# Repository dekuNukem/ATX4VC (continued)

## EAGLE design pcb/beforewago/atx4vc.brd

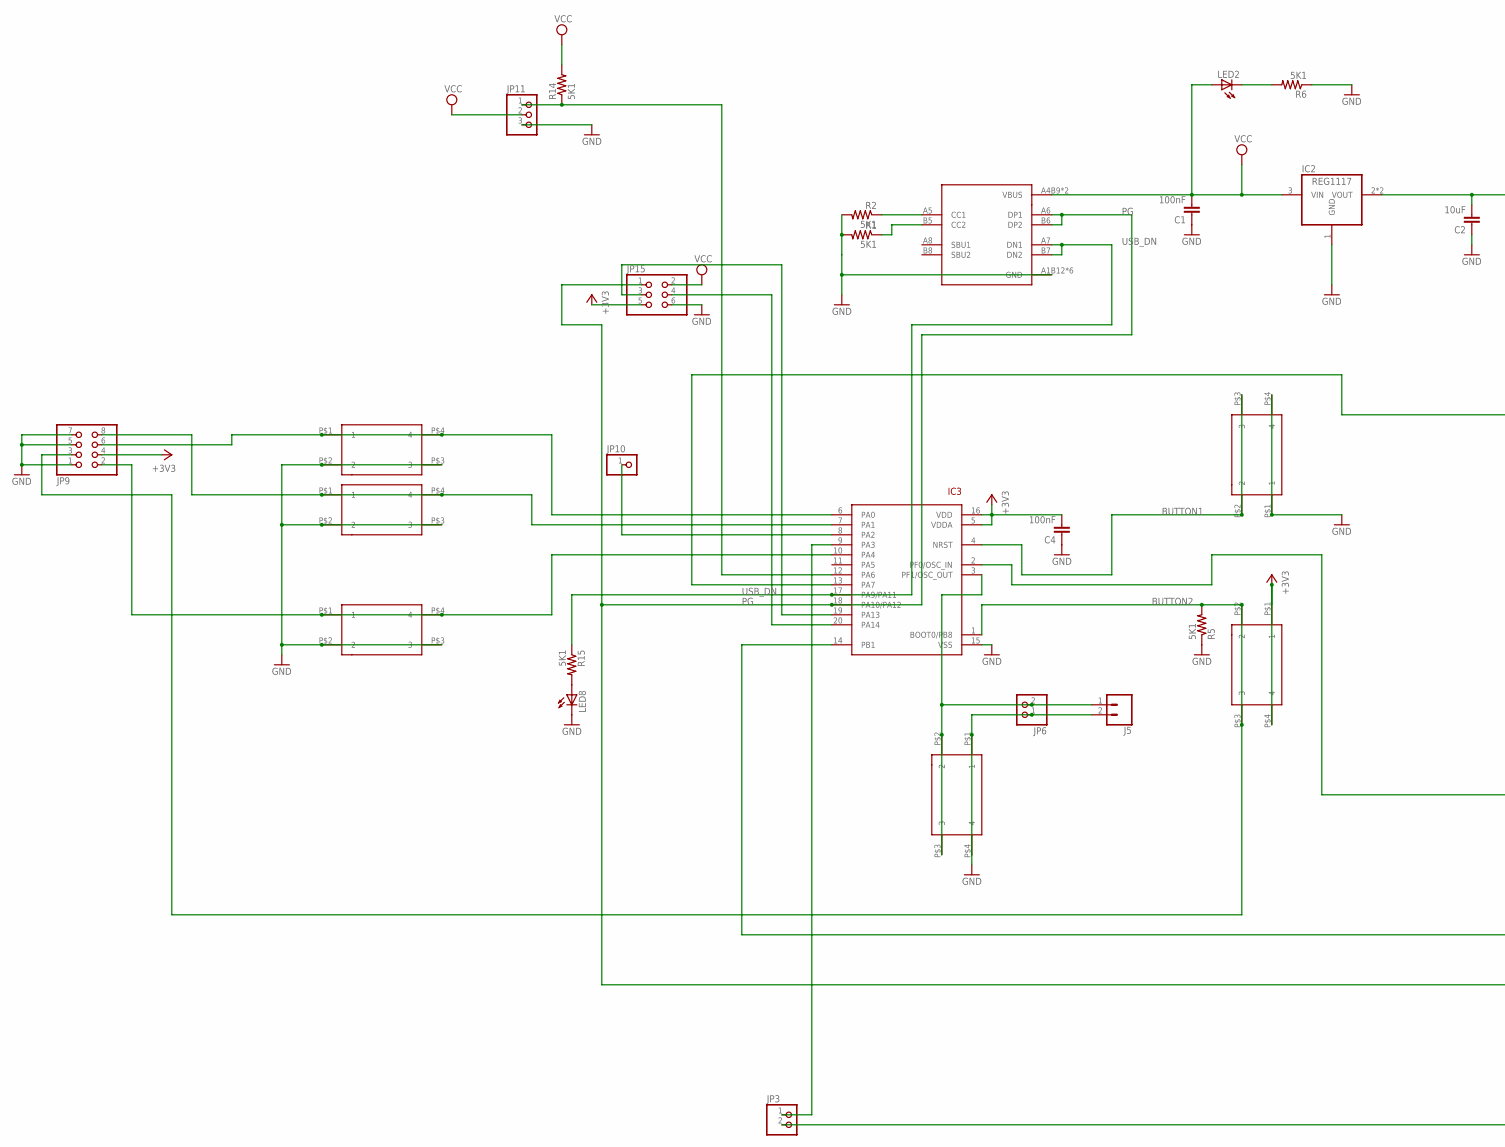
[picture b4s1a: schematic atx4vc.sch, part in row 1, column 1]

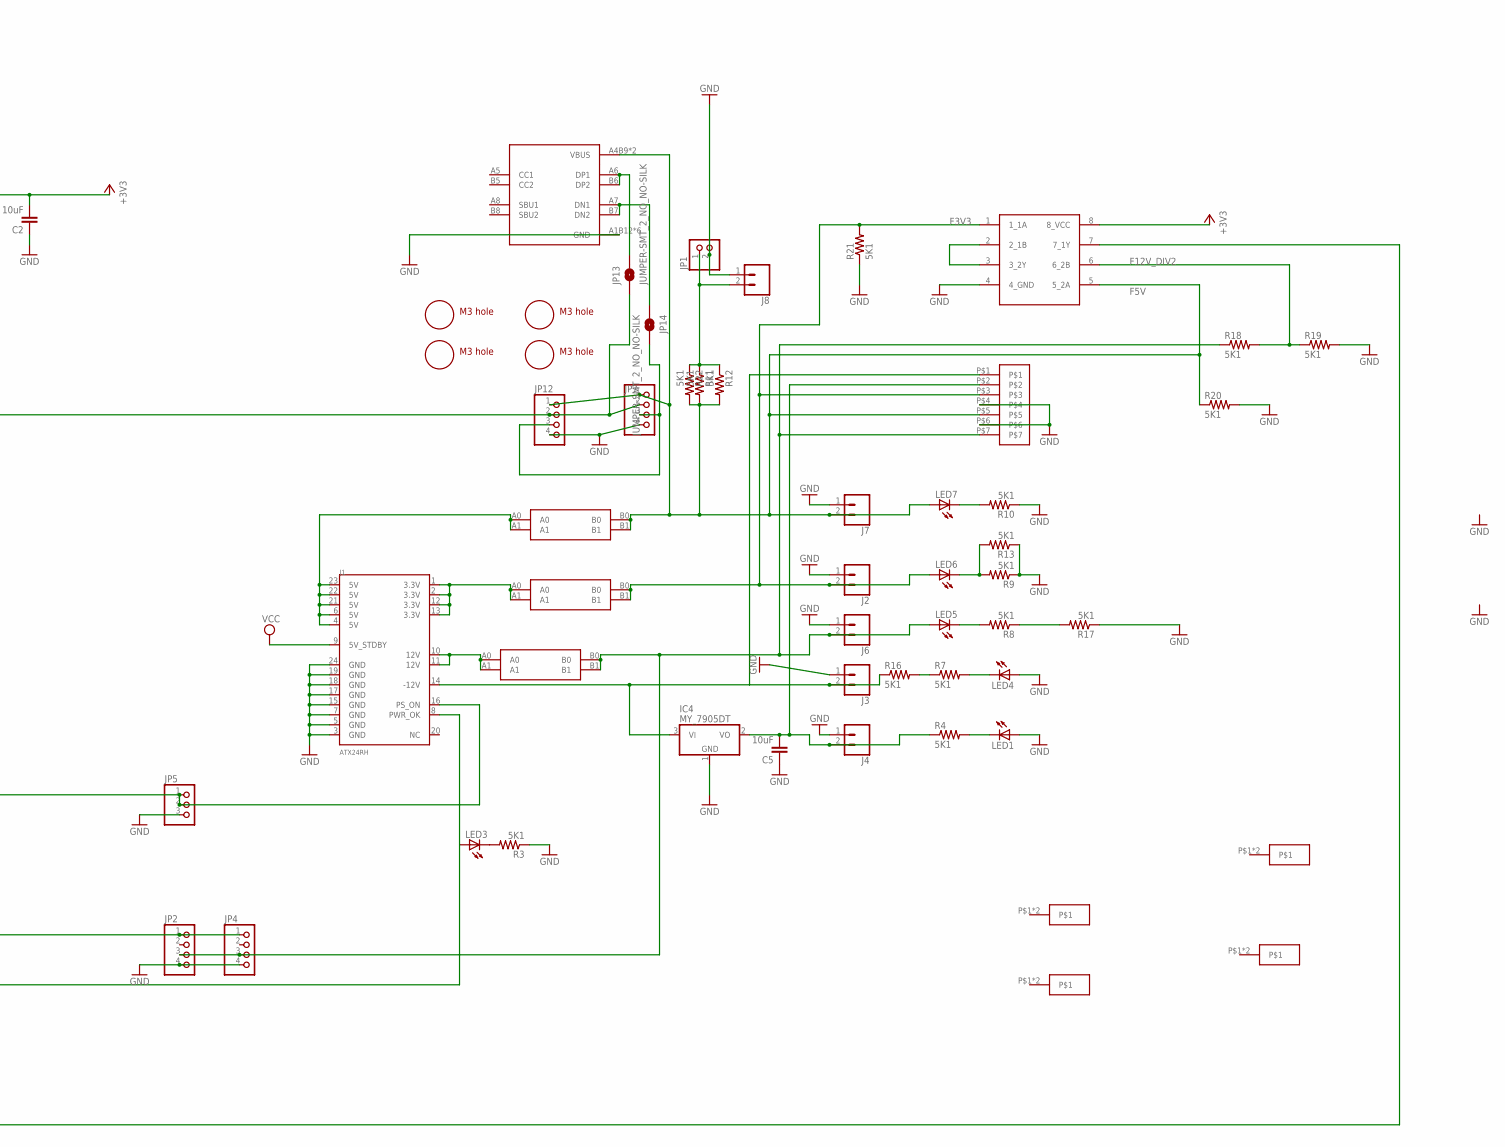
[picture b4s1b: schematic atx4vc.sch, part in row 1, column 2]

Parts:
C1, C4: 100nF; 0805$1
C2, C5: 10uF; 0805$1
IC2: REG1117; SOT223
IC3: STM32F042F4; TSSOP20
IC4: MY_7905DT; ADAFRUIT_TO252
J1: ATX24RH; ATX24_RIGHT_ANGLE
J2, J3, J4, J5, J6, J8: CONN_023.5MM; SCREWTERMINAL-3.5MM-2
J7: CONN_023.5MM-NO_SILK; SCREWTERMINAL-3.5MM-2-NS
JP1, JP3, JP6: PINHD-1X2; 1X02
JP2, JP4: PINHD-1X4; 1X04
JP5: PINHD-1X3:1; 1X03
JP7, JP12: PINHD-1X6; 1X06
JP9: PINHD-2X4; 2X04
JP10: PINHD-1X1CB; 1X01-CLEANBIG
JP11: PINHD-1X3CB; 1X03-CLEANBIG
JP13, JP14: JUMPER-SMT_2_NO_NO-SILK; SMT-JUMPER_2_NO_NO-SILK
JP15: PINHD-2X3; 2X03
LED1, LED2, LED3, LED4, LED5, LED6, LED7, LED8: LEDCHIP-LED0805; CHIP-LED0805
R1, R2, R3, R4, R5, R6, R7, R8, R9, R10, R11, R12, R13, R14, R15, R16, R17, R18, R19, R20, R21, R22: 5K1; 0805
SW1, SW2, SW3, SW4, SW5, SW7: 324_SW; 342_SWICH_FOOT
U1, U2: USBC_16P; USBC_16P_FOOT
U$1, U$2, U$3, U$10: M3_MOUNTING_HOLE; M3_MOUNTING_HOLE_PACK
U$4: VH396; 396_7P
U$5, U$7, U$8: CAR_FUSE_HOLDER3IN1; FUSE_HOLDER_3IN1
U$6: 74LVC2G08; VSSOP08
U$9, U$11, U$12, U$13: WAGO257; WAGL257

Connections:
+3V3: C2.2, C4.2, IC2.2 (VOUT), IC2.4 (VOUT), IC3.5 (VDDA), IC3.16 (VDD), JP9.4, JP15.5, SW4.P$1 (1), SW4.P$4 (4), U$6.8 (8_VCC)
BUTTON1: IC3.4 (NRST), SW3.P$2 (2), SW3.P$3 (3)
BUTTON2: IC3.1 (BOOT0/PB8), JP9.3, R5.2, SW4.P$2 (2), SW4.P$3 (3)
F3V3: J2.2, LED6.A, R21.2, U$4.P$3, U$6.1 (1_1A), U$7.B0, U$7.B1
F5V: J7.2, JP7.1, JP12.1, LED7.A, R11.2, R12.2, R20.1, R22.2, U1.A4B9 (VBUS), U1.B4A9 (VBUS), U$4.P$5, U$6.5 (5_2A), U$8.B0, U$8.B1
F12V: J6.2, JP2.3, JP4.3, LED5.A, R18.1, U$4.P$7, U$5.B0, U$5.B1
F12V_DIV2: R18.2, R19.1, U$6.6 (6_2B)
GND: C1.1, C2.1, C4.1, C5.1, IC2.1 (GND), IC3.15 (VSS), IC4.1 (GND), J1.3 (GND), J1.5 (GND), J1.7 (GND), J1.15 (GND), J1.17 (GND), J1.18 (GND), J1.19 (GND), J1.24 (GND), J2.1, J3.1, J4.1, J5.2, J6.1, J7.1, J8.1, JP1.2, JP2.4, JP4.4, JP5.3, JP6.1, JP7.4, JP9.1, JP9.5, JP9.7, JP11.3, JP12.4, JP15.6, LED1.A, LED4.A, LED8.C, R1.2, R2.2, R3.1, R5.1, R6.1, R9.1, R10.1, R13.1, R17.1, R19.2, R20.2, R21.1, SW1.P$1 (1), SW1.P$4 (4), SW2.P$2 (2), SW2.P$3 (3), SW3.P$1 (1), SW3.P$4 (4), SW5.P$2 (2), SW5.P$3 (3), SW7.P$2 (2), SW7.P$3 (3), U1.A1B12 (GND), U1.B11A12 (GND), U1.P$13 (GND), U1.P$14 (GND), U1.P$15 (GND), U1.P$16 (GND), U2.A1B12 (GND), U2.B11A12 (GND), U2.P$13 (GND), U2.P$14 (GND), U2.P$15 (GND), U2.P$16 (GND), U$4.P$4, U$4.P$6, U$6.4 (4_GND)
unnamed: LED3.C, R3.2
unnamed: IC4.3 (VI), J1.14 (-12V), J3.2, R16.1, U$4.P$1
unnamed: IC3.20 (PA14), JP15.4
unnamed: IC3.19 (PA13), JP15.3
unnamed: LED1.C, R4.2
unnamed: IC3.12 (PA6), JP11.1, R14.1
unnamed: IC3.14 (PB1), JP2.1, JP4.1
unnamed: LED4.C, R7.2
unnamed: LED5.C, R8.2
unnamed: J1.4 (5V), J1.6 (5V), J1.21 (5V), J1.22 (5V), J1.23 (5V), U$8.A0, U$8.A1
unnamed: C5.2, IC4.2 (VO), J4.2, R4.1, U$4.P$2
unnamed: U$6.2 (2_1B), U$6.3 (3_2Y)
unnamed: IC3.6 (PA0), JP9.6, SW2.P$1 (1), SW2.P$4 (4)
unnamed: J1.1 (3.3V), J1.2 (3.3V), J1.12 (3.3V), J1.13 (3.3V), U$7.A0, U$7.A1
unnamed: J8.2, JP1.1, R11.1, R12.1, R22.1
unnamed: LED6.C, R9.2, R13.2
unnamed: LED8.A, R15.2
unnamed: LED7.C, R10.2
unnamed: J1.10 (12V), J1.11 (12V), U$5.A0, U$5.A1
unnamed: IC3.7 (PA1), JP9.8, SW5.P$1 (1), SW5.P$4 (4)
unnamed: IC3.8 (PA2), JP10.1
unnamed: JP3.2, U$6.7 (7_1Y)
unnamed: IC3.2 (PF0/OSC_IN), J1.16 (PS_ON), JP5.1, JP5.2
unnamed: IC3.3 (PF1/OSC_OUT), J5.1, JP6.2, SW1.P$2 (2), SW1.P$3 (3)
unnamed: IC3.10 (PA4), JP9.2, SW7.P$1 (1), SW7.P$4 (4)
unnamed: R7.1, R16.2
unnamed: LED2.C, R6.2
unnamed: R1.1, U2.B5 (CC2)
unnamed: R8.1, R17.2
unnamed: R2.1, U2.A5 (CC1)
unnamed: JP13.2, U1.A6 (DP1), U1.B6 (DP2)
unnamed: IC3.13 (PA7), JP7.2, JP12.2, JP13.1
unnamed: JP14.1, U1.A7 (DN1), U1.B7 (DN2)
unnamed: JP7.3, JP12.3, JP14.2
unnamed: IC3.9 (PA3), JP3.1
PG: IC3.18 (PA10/PA12), J1.8 (PWR_OK), JP15.1, LED3.A, U2.A6 (DP1), U2.B6 (DP2)
USB_DN: IC3.17 (PA9/PA11), R15.1, U2.A7 (DN1), U2.B7 (DN2)
VCC: C1.2, IC2.3 (VIN), J1.9 (5V_STDBY), JP11.2, JP15.2, LED2.A, R14.2, U2.A4B9 (VBUS), U2.B4A9 (VBUS)

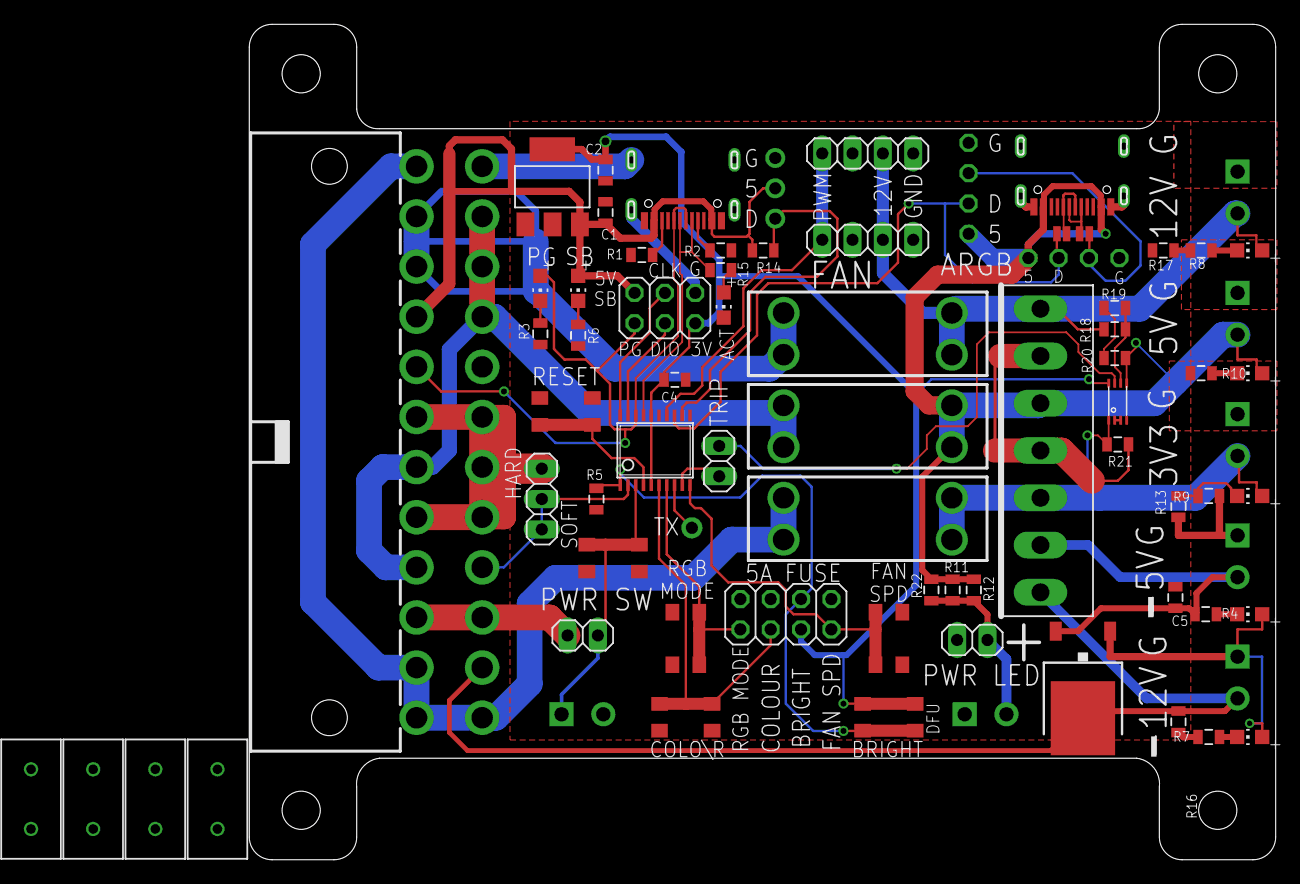
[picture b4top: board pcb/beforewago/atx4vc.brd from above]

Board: 2 copper layers, 86.0 x 70.0 mm, 80 parts (0 on the bottom side), 46 nets.

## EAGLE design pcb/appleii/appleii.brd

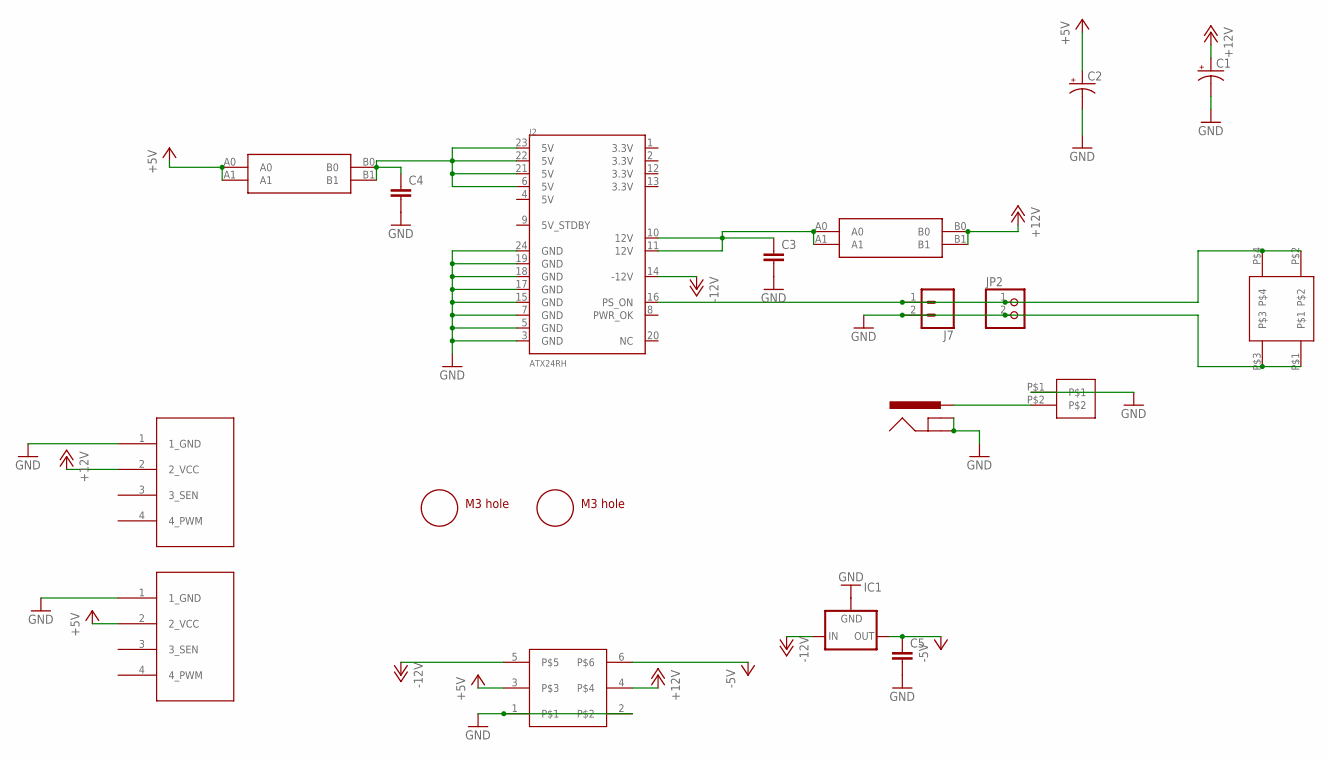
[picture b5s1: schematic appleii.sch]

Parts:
C1, C2: CPOL-USE5-10.5; E5-10,5
C3, C4, C5: C5/2.5; C5B2.5
IC1: 79XXS
J1: POWER_JACKPTH; POWER_JACK_PTH
J2: ATX24RH; ATX24_RIGHT_ANGLE
J7: CONN_023.5MM-NO_SILK; SCREWTERMINAL-3.5MM-2-NS
JP1, JP4: 4PIN_FAN; 1X04
JP2: PINHD-1X2; 1X02
U$1, U$3: M3_MOUNTING_HOLE; M3_MOUNTING_HOLE_PACK
U$2, U$8: CAR_FUSE_HOLDER3IN1; FUSE_HOLDER_3IN1
U$4: APPLEII
U$5: ROCK_SW; ROCK_SWITCH
U$7: VH396_2P; 396_2P

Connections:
+5V: C2.+, JP4.2 (2_VCC), U$4.3, U$8.A0, U$8.A1
+12V: C1.+, JP1.2 (2_VCC), U$2.B0, U$2.B1, U$4.4
-5V: C5.1, IC1.OUT, U$4.6
-12V: IC1.IN, J2.14 (-12V), U$4.5
GND: C1.-, C2.-, C3.2, C4.2, C5.2, IC1.GND, J1.GND, J1.GNDBREAK, J2.3 (GND), J2.5 (GND), J2.7 (GND), J2.15 (GND), J2.17 (GND), J2.18 (GND), J2.19 (GND), J2.24 (GND), J7.2, JP1.1 (1_GND), JP2.2, JP4.1 (1_GND), U$4.1, U$4.2, U$5.P$1, U$5.P$3, U$7.P$1
unnamed: J1.PWR, U$7.P$2
unnamed: J2.16 (PS_ON), J7.1, JP2.1, U$5.P$2, U$5.P$4
unnamed: C4.1, J2.6 (5V), J2.21 (5V), J2.22 (5V), J2.23 (5V), U$8.B0, U$8.B1
unnamed: C3.1, J2.10 (12V), J2.11 (12V), U$2.A0, U$2.A1

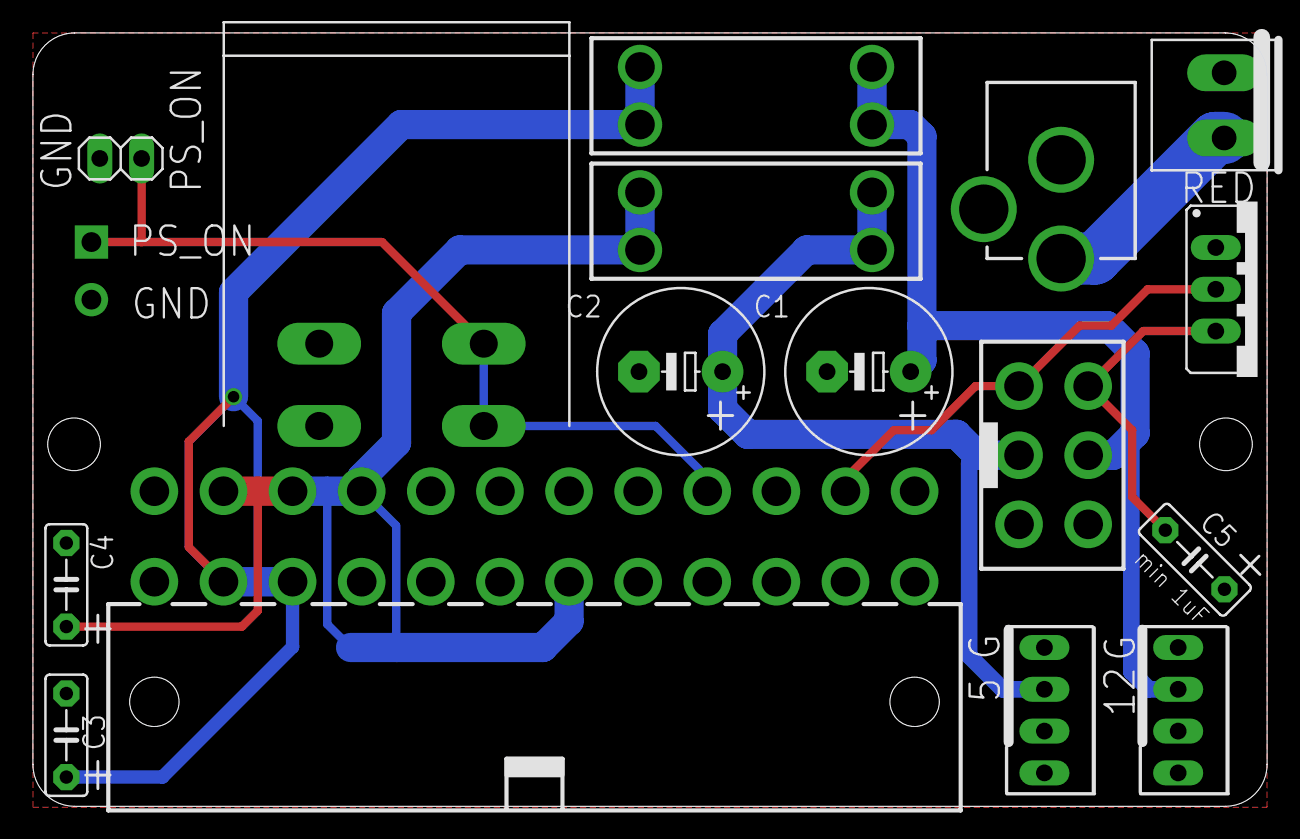
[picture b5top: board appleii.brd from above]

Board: 2 copper layers, 75.0 x 47.0 mm, 19 parts (0 on the bottom side), 9 nets.

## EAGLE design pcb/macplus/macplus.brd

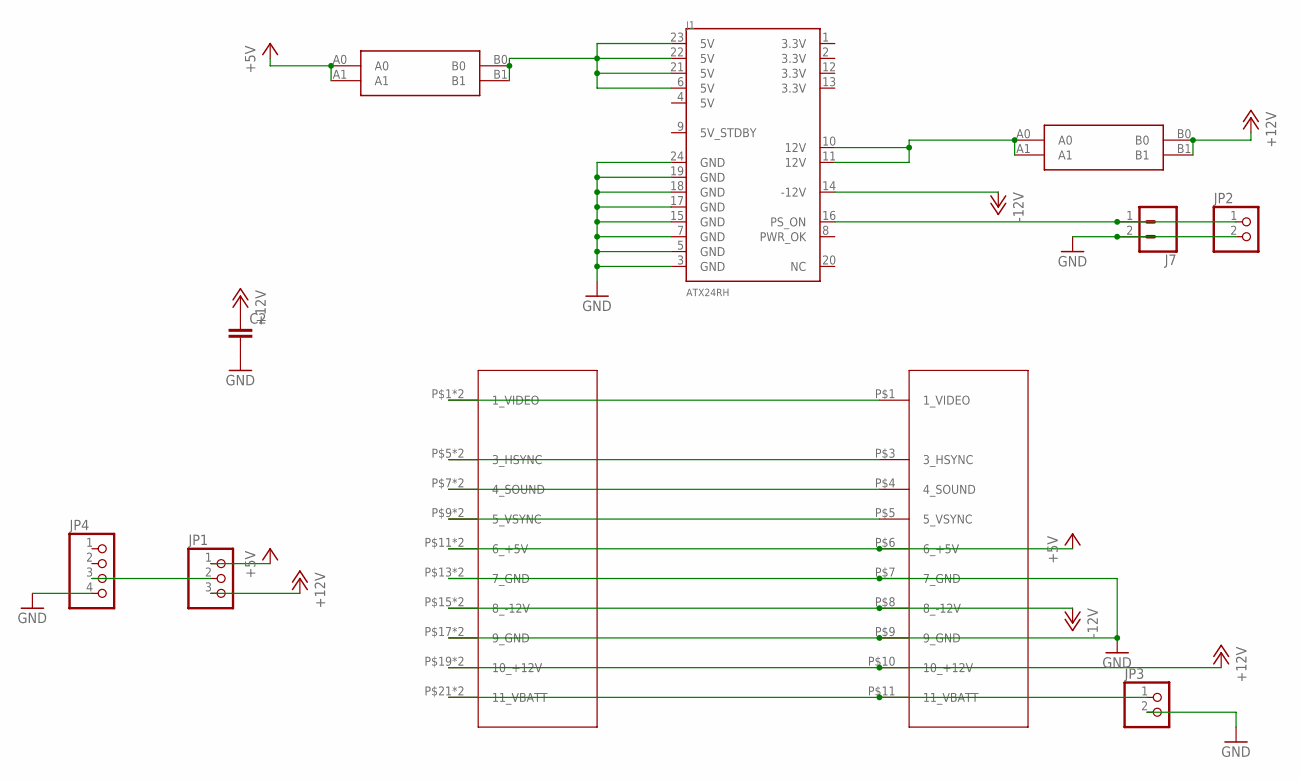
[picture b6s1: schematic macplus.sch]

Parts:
C2: C5/2.5; C5B2.5
J1: ATX24RH; ATX24_STRAIGHT
J7: CONN_023.5MM-NO_SILK; SCREWTERMINAL-3.5MM-2-NS
JP1: PINHD-1X3; 1X03
JP2, JP3: PINHD-1X2; 1X02
JP4: PINHD-1X4; 1X04
U$1: MACPLUS; 396_10P
U$2, U$8: CAR_FUSE_HOLDER3IN1; FUSE_HOLDER_3IN1
U$3: 3.96_FEM; 3.96_FEMALE_GAP

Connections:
+5V: JP1.1, U$1.P$6 (6_+5V), U$3.P$11 (6_+5V), U$3.P$12 (6_+5V), U$8.A0, U$8.A1
+12V: C2.1, JP1.3, U$1.P$10 (10_+12V), U$2.B0, U$2.B1, U$3.P$19 (10_+12V), U$3.P$20 (10_+12V)
-12V: J1.14 (-12V), U$1.P$8 (8_-12V), U$3.P$15 (8_-12V), U$3.P$16 (8_-12V)
GND: C2.2, J1.3 (GND), J1.5 (GND), J1.7 (GND), J1.15 (GND), J1.17 (GND), J1.18 (GND), J1.19 (GND), J1.24 (GND), J7.2, JP2.2, JP3.2, JP4.4, U$1.P$7 (7_GND), U$1.P$9 (9_GND), U$3.P$13 (7_GND), U$3.P$14 (7_GND), U$3.P$17 (9_GND), U$3.P$18 (9_GND)
unnamed: U$1.P$1 (1_VIDEO), U$3.P$1 (1_VIDEO), U$3.P$2 (1_VIDEO)
unnamed: U$1.P$3 (3_HSYNC), U$3.P$5 (3_HSYNC), U$3.P$6 (3_HSYNC)
unnamed: U$1.P$4 (4_SOUND), U$3.P$7 (4_SOUND), U$3.P$8 (4_SOUND)
unnamed: U$1.P$5 (5_VSYNC), U$3.P$9 (5_VSYNC), U$3.P$10 (5_VSYNC)
unnamed: J1.16 (PS_ON), J7.1, JP2.1
unnamed: J1.6 (5V), J1.21 (5V), J1.22 (5V), J1.23 (5V), U$8.B0, U$8.B1
unnamed: JP1.2, JP4.3
unnamed: J1.10 (12V), J1.11 (12V), U$2.A0, U$2.A1
unnamed: JP3.1, U$1.P$11 (11_VBATT), U$3.P$21 (11_VBATT), U$3.P$22 (11_VBATT)

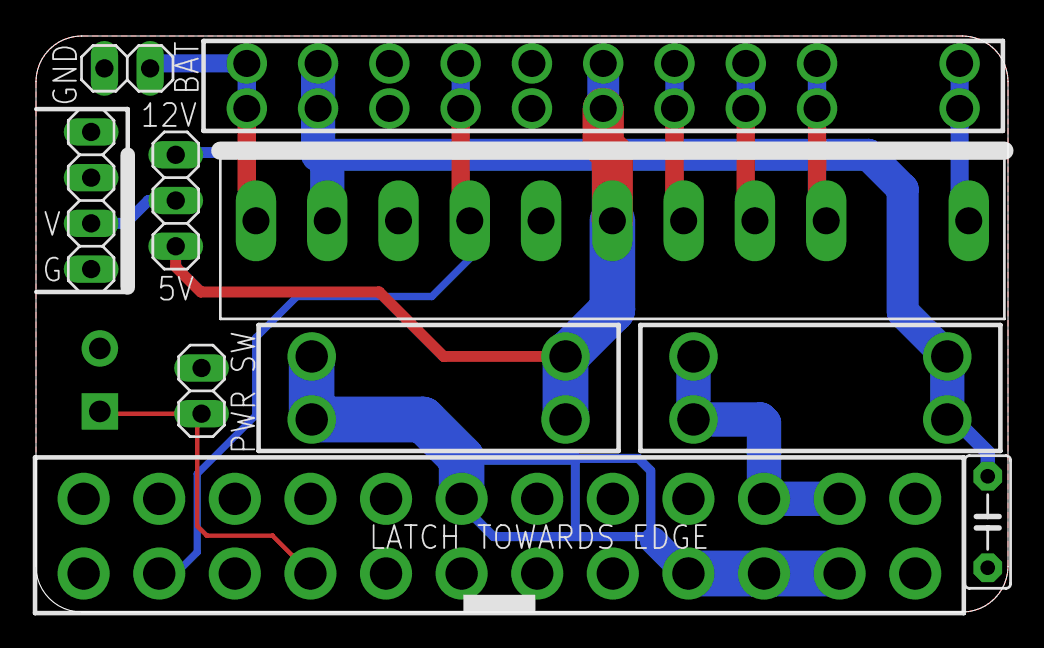
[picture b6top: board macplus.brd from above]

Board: 2 copper layers, 54.0 x 32.0 mm, 11 parts (0 on the bottom side), 13 nets.

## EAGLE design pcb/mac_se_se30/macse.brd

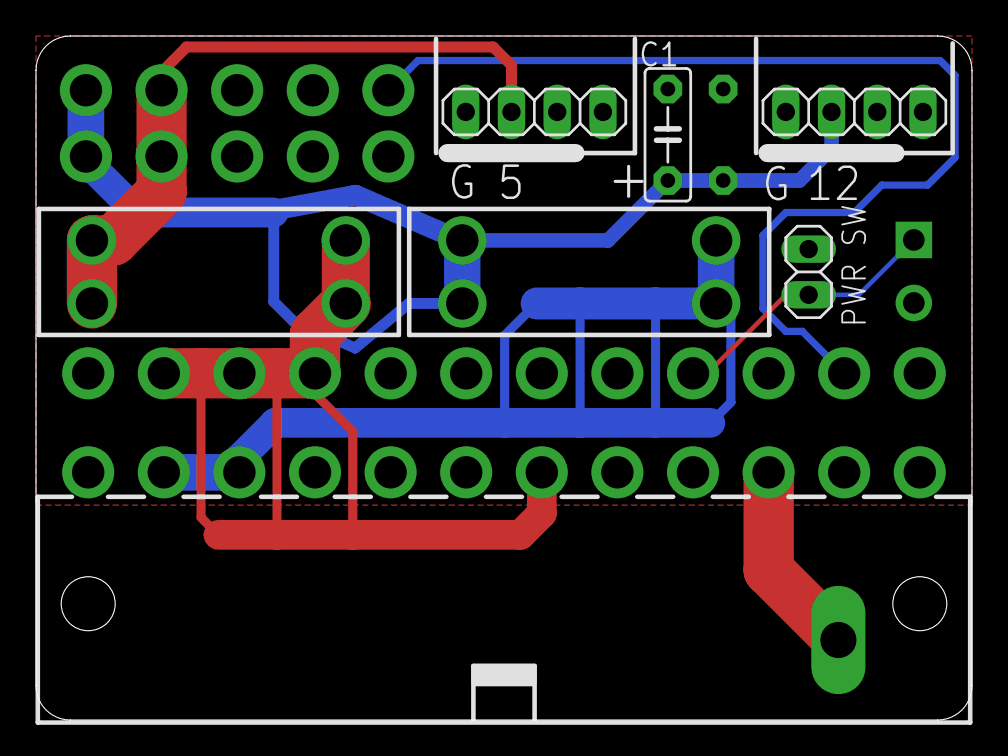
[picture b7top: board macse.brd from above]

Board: 2 copper layers, 52.0 x 38.0 mm, 11 parts (1 on the bottom side), 7 nets.

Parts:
C1, C2: C5B2.5
J2: ATX24RH; ATX24_RIGHT_ANGLE
J7: SCREWTERMINAL-3.5MM-2-NS
JP1, JP3: 1X04
JP2: 1X02
TP1: PTR1PAD1-20Y; P1-20Y
U$1: MACSE; MACSE_10P_STRAIGHT
U$2, U$8: CAR_FUSE_HOLDER3IN1; FUSE_HOLDER_3IN1

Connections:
+5V: JP3.3, U$1.4, U$1.9, U$8.A0, U$8.A1
+12V: C1.1, C2.1, JP1.3, U$1.5, U$1.10, U$2.B0, U$2.B1
-12V: J2.14, U$1.6
GND: C1.2, C2.2, J2.3, J2.5, J2.7, J2.15, J2.17, J2.18, J2.19, J2.24, J7.2, JP1.4, JP2.2, JP3.4, TP1.TP, U$1.1, U$1.2, U$1.3, U$1.7, U$1.8
unnamed: J2.16, J7.1, JP2.1
unnamed: J2.6, J2.21, J2.22, J2.23, U$8.B0, U$8.B1
unnamed: J2.10, J2.11, U$2.A0, U$2.A1

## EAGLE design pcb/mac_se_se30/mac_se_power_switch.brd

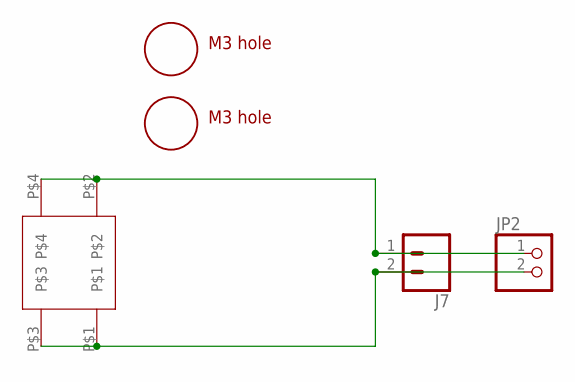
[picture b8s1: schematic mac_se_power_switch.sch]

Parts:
J7: CONN_023.5MM-NO_SILK; SCREWTERMINAL-3.5MM-2-NS
JP2: PINHD-1X2/90; 1X02/90
U$1: ROCK_SW; ROCK_SWITCH
U$2, U$3: M3_MOUNTING_HOLE; M3_MOUNTING_HOLE_PACK

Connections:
unnamed: J7.2, JP2.2, U$1.P$1, U$1.P$3
unnamed: J7.1, JP2.1, U$1.P$2, U$1.P$4

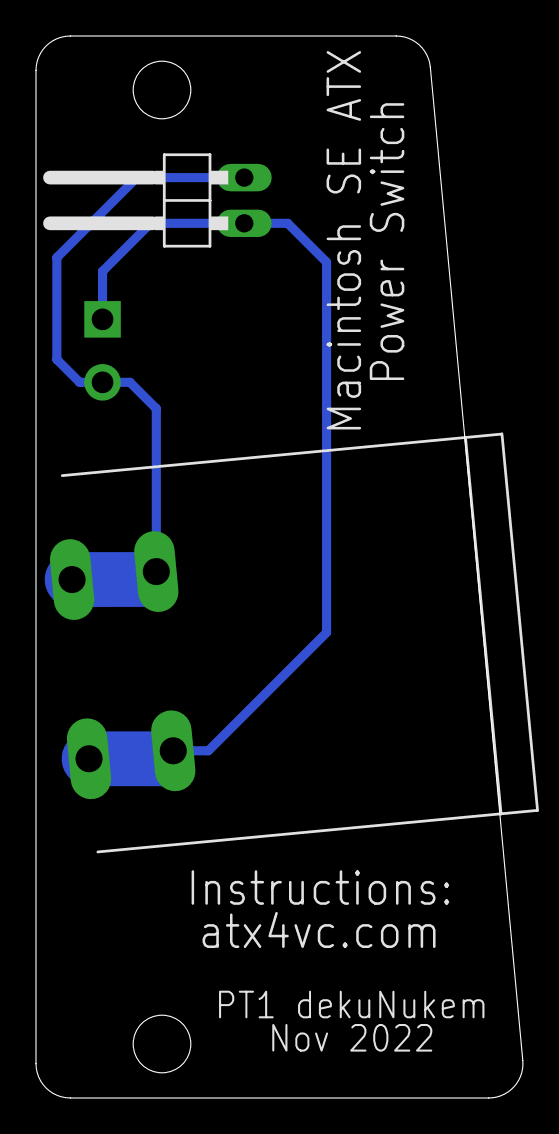
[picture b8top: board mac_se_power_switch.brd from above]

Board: 2 copper layers, 27.1 x 59.0 mm, 5 parts (0 on the bottom side), 2 nets.

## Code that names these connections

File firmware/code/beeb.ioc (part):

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Mcu.Name=STM32F042F6Px
Mcu.Package=TSSOP20
Mcu.UserName=STM32F042F6Px
PA0.GPIOParameters=GPIO_PuPd,GPIO_Label
PA0.GPIO_Label=BTN_COLOR
PA0.GPIO_PuPd=GPIO_PULLUP
PA0.Signal=GPIO_Input
PA1.GPIOParameters=GPIO_PuPd,GPIO_Label
PA1.GPIO_Label=BTN_RGB_MODE
PA1.GPIO_PuPd=GPIO_PULLUP
PA1.Signal=GPIO_Input
PA10.GPIOParameters=GPIO_PuPd,GPIO_Label
PA10.GPIO_Label=ATX_PG
PA10.GPIO_PuPd=GPIO_PULLDOWN
PA10.Signal=GPIO_Input
PA13.Mode=Serial_Wire
PA13.Signal=SYS_SWDIO
PA14.Mode=Serial_Wire
PA14.Signal=SYS_SWCLK
PA2.Mode=Half_duplex(single_wire_mode)
PA2.Signal=USART2_TX
PA3.GPIOParameters=PinState,GPIO_PuPd,GPIO_Label,GPIO_ModeDefaultOutputPP
PA3.GPIO_Label=DEBUG
PA3.GPIO_ModeDefaultOutputPP=GPIO_MODE_OUTPUT_OD
PA3.GPIO_PuPd=GPIO_PULLUP
PA3.PinState=GPIO_PIN_SET
PA3.Signal=GPIO_Output
PA4.GPIOParameters=GPIO_PuPd,GPIO_Label
PA4.GPIO_Label=BTN_FANSPEED
PA4.GPIO_PuPd=GPIO_PULLUP
PA4.Signal=GPIO_Input
PA5.Mode=TX_Only_Simplex_Unidirect_Master
PA5.Signal=SPI1_SCK
PA6.GPIOParameters=PinState,GPIO_PuPd,GPIO_Label,GPIO_ModeDefaultOutputPP
PA6.GPIO_Label=ONEWIRE_DATA
PA6.GPIO_ModeDefaultOutputPP=GPIO_MODE_OUTPUT_OD
PA6.GPIO_PuPd=GPIO_PULLUP
PA6.PinState=GPIO_PIN_SET
PA6.Signal=GPIO_Output
PA7.Mode=TX_Only_Simplex_Unidirect_Master
PA7.Signal=SPI1_MOSI
PA9.GPIOParameters=GPIO_Label
PA9.GPIO_Label=USER_LED
PA9.Signal=GPIO_Output
PB1.GPIOParameters=GPIO_ModeDefaultPP,GPIO_PuPd
PB1.GPIO_ModeDefaultPP=GPIO_MODE_AF_OD
PB1.GPIO_PuPd=GPIO_NOPULL
PB1.Signal=S_TIM14_CH1
PB8.GPIOParameters=GPIO_PuPd,GPIO_Label
PB8.GPIO_Label=BTN_BRIGHTNESS
PB8.GPIO_PuPd=GPIO_PULLDOWN
PB8.Signal=GPIO_Input
PF0-OSC_IN.GPIOParameters=PinState,GPIO_Label,GPIO_ModeDefaultOutputPP
PF0-OSC_IN.GPIO_Label=PWR_ON
PF0-OSC_IN.GPIO_ModeDefaultOutputPP=GPIO_MODE_OUTPUT_OD
PF0-OSC_IN.PinState=GPIO_PIN_SET
PF0-OSC_IN.Signal=GPIO_Output
PF1-OSC_OUT.GPIOParameters=GPIO_PuPd,GPIO_Label
PF1-OSC_OUT.GPIO_Label=BTN_POWER
PF1-OSC_OUT.GPIO_PuPd=GPIO_PULLUP
PF1-OSC_OUT.Signal=GPIO_Input
RCC.SYSCLKFreq_VALUE=37333333.33333333
RCC.SYSCLKSource=RCC_SYSCLKSOURCE_PLLCLK
board=custom

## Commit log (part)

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2022-07-18 added plate and pcb files
2022-07-18 working on PCB
2022-07-18 pcb done sent to fab
2022-07-19 removed unneeded files
2022-07-25 adjusted pcb
2022-07-25 writing button debouncing firmware
2022-07-26 button working
2022-08-09 ws2812 working
2022-08-09 working on new ATX PCB
2022-08-10 atx board finished
2022-08-10 updated changelog, adjusted silkscreen
2022-08-14 updated atx adaptor plate, removed terminal block GND thermals
2022-08-14 updated atx board
2022-08-15 removed pot and added buttons and header
2022-08-19 updated plate
2022-08-22 making backlight PCB
2022-08-23 atx rgb done, updated atx psu board too
2022-08-23 cleaned up files
2022-08-28 added button reading and 16ms timer interupt
2022-08-30 updated pcb
2022-08-30 fixed led board silkscreen, changed ATX4VC to use PG signal
2022-08-30 added UART RX header, brightness button shared with DFU button
2022-08-30 fan pwm working
2022-08-30 rgb led working
2022-08-31 button read working
2022-08-31 optimised RGB LED write to reduce RAM usage
2022-08-31 button count working
2022-08-31 eeprom working
2022-08-31 cleaned up code
2022-08-31 adjusted fuse holder on PCB
2022-08-31 fan speed step done
2022-08-31 before testing iwdg
2022-08-31 added pwr_good check on boot
2022-08-31 updated pcb headers
2022-08-31 added hsv to rgb conversion
2022-08-31 added color and brightness adjustment
2022-09-01 station rainbow working
2022-09-01 added rolling rainbow and crossfade
2022-09-01 working on breathing led
2022-09-01 breathing led done
2022-09-01 added compatibilty with flip switch power
2022-09-01 added button autorepeat
2022-09-01 adjust brightness scale
2022-09-01 added idwg
2022-09-01 added selector jumper for power-on detect
2022-09-01 cleanup
2022-09-01 adjusted power button and power LED
2022-09-03 optimised traces routing for current carrying
2022-09-03 minor cleanup
2022-09-03 updated PCB to use car fuse holder
2022-09-03 moved bbc files to its own repo
2022-09-03 added readme
2022-09-04 added dual fan and ARGB headers, ready for new run
2022-09-09 fixed fuse holder footprint
2022-09-22 troubleshooting coolermaster RGB bug
2022-09-22 adjusted ARGB timing
2022-09-22 added ds18b20 header
2022-09-22 ds18b20 working
2022-09-22 added indicator LED
2022-09-22 adjusted LED resistor value, optimised GND plane
2022-09-26 moved ARGB header, removed GND thermals, jumper pad on USBC data lines, finishing touches
2022-09-26 wired to softpower by default
2022-09-26 pretty much done
2022-09-27 added cafe readme
2022-09-27 changed to current name
2022-09-29 added new rolling dim animation, fixing a bug
2022-09-29 fixed interrupt latency bug
2022-09-30 working on power-up fade in
2022-09-30 added startup-fadein
2022-09-30 optimising rolling dim
2022-09-30 added startup fadein in rolling dim
2022-09-30 fixed animation timing issue
2022-09-30 fixed a bug
2022-09-30 fixed power up animation detect
2022-09-30 fixed power up fade in timing
2022-10-05 writing
2022-10-05 pretty much ready
2022-10-05 added table of contents
2022-10-07 added user LED feedback and adjusted button debouncing
2022-10-07 refined hard power support
2022-10-08 added ds18b20 read
2022-10-08 added 50C fan curve
2022-10-08 fan curve feature added, working on blinking lights
2022-10-08 fan curve and light blink done
2022-10-08 adjusted blink brightness
2022-10-11 moved argb header to make more room
2022-10-11 cleaned up PCB
2022-10-11 more concise wording
2022-10-20 updated instructions
2022-10-20 added dfu file
2022-10-30 added sticker label template
2022-10-30 added sticker photo
2022-11-07 added sticker instruction
2022-11-09 working on mac plus adaptor
2022-11-09 mac plus adaptor pretty much done
2022-11-11 working on mac SE adaptor
2022-11-11 mac SE adaptor done
2022-11-11 added mac SE power board
2022-11-11 getting ready for a PCB run
2022-11-12 added more photos
2022-11-14 clean up wording
2022-11-19 adding power connector and fuse detect
2022-11-22 updated doc
2022-11-23 updated mac plus atx adaptor
2022-11-24 updating mac SE atx adaptor
2022-11-24 updated mac SE pcb
2022-11-24 finishing touches
2022-11-24 updated switch footprint
2022-11-25 added appleii
2022-11-25 working on appleii
2022-11-26 updated silkscreen and switched to terminal block for power input
2022-12-02 updated se board
2022-12-05 adding device-specifc doc
2022-12-06 changed name to ATX4VC Pico
2022-12-06 working on doc
2022-12-10 writing idoc
2022-12-10 writing docs
2022-12-10 added toc
2022-12-11 getting ready for tindie listing
2022-12-12 moved picoPSU adaptor to its own repo at PicoRC
2022-12-13 updated flip switch footprint
2022-12-19 updated library
2023-02-21 mentions picoRC
2023-03-09 updated fuse detect chip trace
2023-03-09 added datasheet
2023-03-09 switched to WAGO connectors
2023-03-09 moved ARGB header
2023-03-09 adjusted ARGB header
2023-03-27 working on seperate MCU version
2023-03-27 working on daughterboard
2023-04-03 updated instruction
2023-04-03 working on new version
2023-04-04 new daughterboard
2023-04-05 cleaned up traces
2023-04-05 added edgepad
2023-04-06 updated lbr
2023-04-06 added 5VSB to terminal block, cleaned up files
2023-04-07 updated silkscreen
2023-04-07 added information about new revision
2023-04-11 adjusted fuse position
2023-04-11 fixed a wrong signal
2023-04-11 added pullup on 1wire, gnd pour cleanup
2023-04-11 moved pin headers to the outer edge
2023-04-11 freed up more space
2023-04-18 finishing touches before production run
2023-05-10 updated photos for new version
2023-05-10 fix typos
2023-05-11 added MCU daughtboard instructions
2023-05-18 added PG on terminal block, moved things around
2023-06-01 adding more caps
2023-06-01 new run
2023-06-27 minor adjust
2023-08-14 adjust screw location, clean up traces
2023-11-27 added power LED resistor bypass
2023-12-27 minor adjustments for next production run
2023-12-27 equal dimension
2023-12-27 adjusted snapoff holes
2024-01-10 adjusted hole size
2024-01-11 new production run
2024-03-04 updated photos
2024-05-23 working on updates
2024-05-26 working on update
2024-06-02 rail silkscreen on bottom
2024-10-09 trying out power ic
2024-10-14 soft power ic tested working
2024-10-28 using github pages
2026-04-01 update doc
2026-06-30 added kicad version
2026-06-30 clean up kicad PCB
